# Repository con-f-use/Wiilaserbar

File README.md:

Wiilaserbar
=================

A driver board, case and holder for infrared lasers meant to replace the sensor bar of a Nintendo Wii. 

Be VERY CAREFUL in selecting the output power. Infrared lasers cannot be seen by the naked eye no matter the 
power. They can permanently damage your eyes even at less then 1mW!!! You might blind yourself in an instant!

This is a replacement for the Wii sensor bar. The populatd board powers two infrared laser diode modules. 
These in turn project infrared dots on a surface that the Wiimotes can pick up on just as they were standard
infrared diodes of the "sensor" bar. You can buy infrared laser diode modules on eBay or Aliexpress cheaply.
I used cheap 890nm modules from China said to emit 30mW (the output power with mine was exaggerated -
actually measured power at a university lab was ~2mW).

The driver board was done in KiCAD while the case was 3D modelled in FreeCAD and printed on a LulzBot Mini.

ToDo
==========

 - Case could be smaller and have snapins for the board

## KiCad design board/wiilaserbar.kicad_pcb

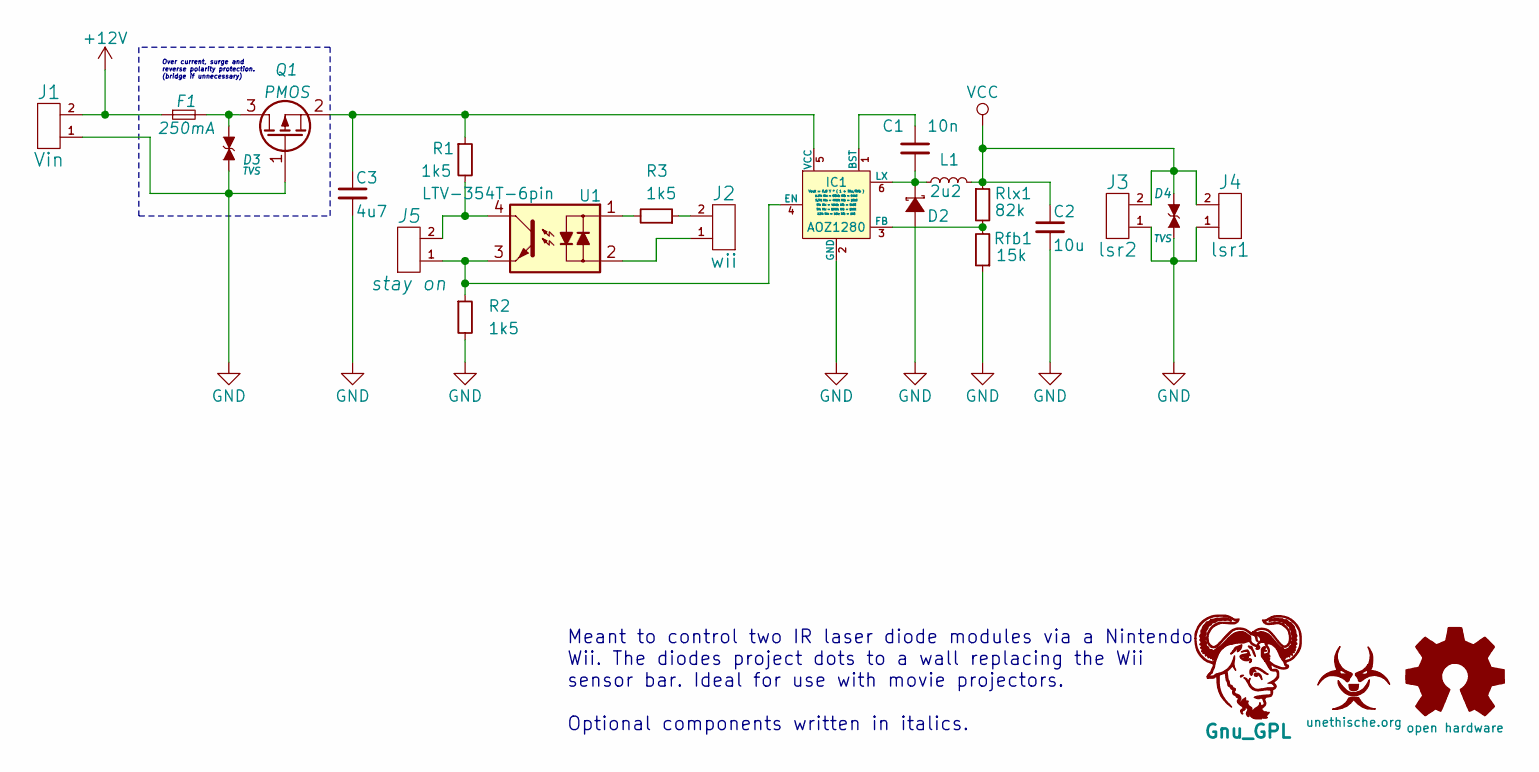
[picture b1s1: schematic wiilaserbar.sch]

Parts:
C1: 10n; C_0603_HandSoldering
C2: 10u; C_0603_HandSoldering
C3: 4u7; C_0603_HandSoldering
D2: D_Schottky_Small; DIODE_POWERMITE
D3, D4: TVS; SOD-523
F1: 250mA; SMD-1206_Pol
IC1: AOZ1280; SOT-23-6
J1: Vin; kk100_22-23-2021
J2: wii; kk100_22-23-2021
J3: lsr2; kk100_22-23-2021
J4: lsr1; kk100_22-23-2021
J5: stay on; PINHEAD1-2
L1: 2u2; R_0805_HandSoldering
LO1: Gnu_GPL; gnu_gpl
LOGO1: open hardware; Logo_silk_OSHW_6x6mm
O1: unethische.org; unethi_silk
Q1: PMOS; SOT-23
R1, R2, R3: 1k5; R_0603_HandSoldering
Rfb1: 15k; R_0603_HandSoldering
Rlx1: 82k; R_0603_HandSoldering
U1: LTV-354T-6pin; Optocoupler_SMD_HandSoldering_KPC357_LTV35x_PC357_SingleCha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

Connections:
+12V: F1.1, J1.2
GND: C2.2, C3.2, D2.2 (A), D3.2 (K), D4.2 (K), IC1.2 (GND), J1.1, J3.1, J4.1, Q1.1 (G), R2.2, Rfb1.1; also elsewhere on the board
unnamed: C1.1, IC1.1 (BST)
unnamed: C1.2, D2.1 (K), IC1.6 (LX), L1.1
unnamed: C3.1, IC1.5 (VCC), Q1.2 (S), R1.1
unnamed: D3.1 (A), F1.2, Q1.3 (D)
unnamed 6: IC1.3 (FB), Rfb1.2, Rlx1.2; also elsewhere on the board
unnamed: IC1.4 (EN), J5.1, R2.1, U1.3
unnamed: J2.1, U1.2
unnamed: J2.2, R3.1
unnamed: J5.2, R1.2, U1.4
unnamed: R3.2, U1.1
VCC: C2.1, D4.1 (A), J3.2, J4.2, L1.2, Rlx1.1; also elsewhere on the board

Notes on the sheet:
Meant to control two IR laser diode modules via a Nintendo Wii. The diodes project dots to a wall replacing the Wii sensor bar. Ideal for use with movie projectors. Optional components written in italics.
Over current, surge and reverse polarity protection. (bridge if unnecessary)

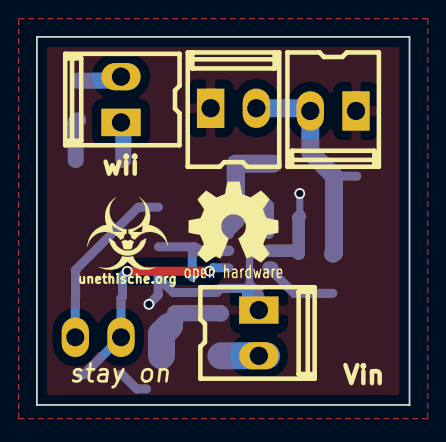
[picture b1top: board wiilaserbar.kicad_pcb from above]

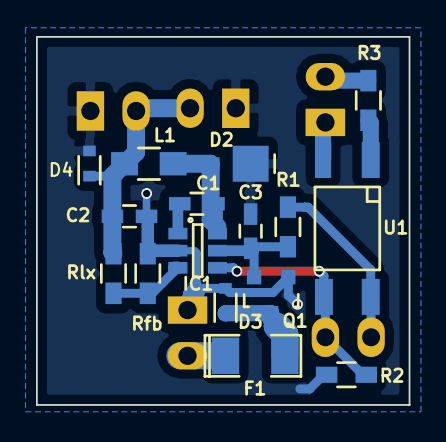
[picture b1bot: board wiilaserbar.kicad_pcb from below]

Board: 2 copper layers, 20.7 x 20.4 mm, 24 parts (16 on the bottom side), 13 nets.

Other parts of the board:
Rfb: 15k; R_0603_HandSoldering
Rlx: 82k; R_0603_HandSoldering

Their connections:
GND: Rfb.1; also elsewhere on the board
unnamed 6: Rfb.2, Rlx.2; also elsewhere on the board
VCC: Rlx.1; also elsewhere on the board

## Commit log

2015-11-07 Cleanup of old files
2015-11-07 Used Software listed in README.md
2015-11-07 Added todo section to README.md
